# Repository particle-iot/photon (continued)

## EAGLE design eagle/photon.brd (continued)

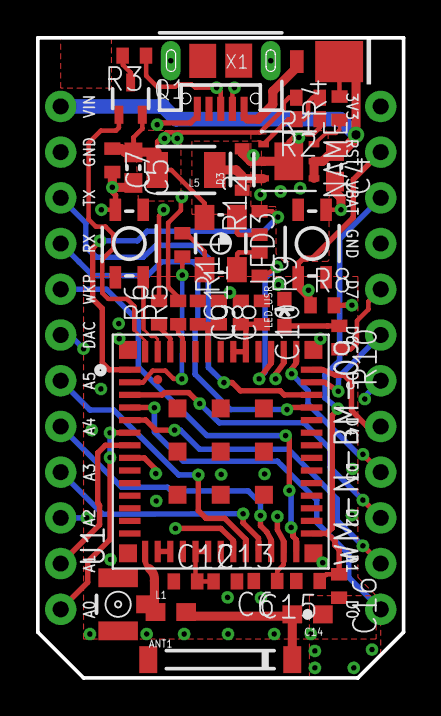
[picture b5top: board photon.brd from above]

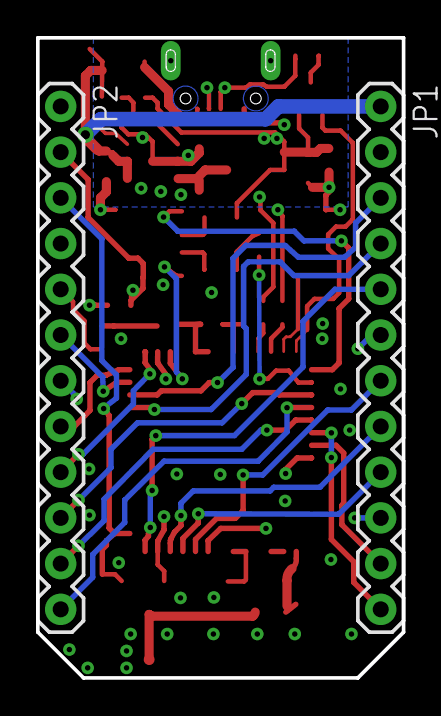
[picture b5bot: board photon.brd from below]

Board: 4 copper layers, 20.3 x 35.6 mm, 41 parts (2 on the bottom side), 46 nets.

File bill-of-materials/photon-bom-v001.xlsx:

| SPARK SKU |  | Spark Photon
 | BOM VERSION |  | v0.0.1
 | Qty | Device | Minimum Specification | Package/Case | Part Designator | MFG. | MFG. PN
 | 1 | ANTENNA | 2.4GHz, Ceramic | 8mm x 1mm | ANT1 | ACX | US PN = 2500AT44M0400E Asia PN = AT8010-E2R9HAA
 | 2 | CERAMIC CAPACITOR | 22uF, Ceramic, 10V, 10%, X5R | 0603 | C4, C5
 | 6 | CERAMIC CAPACITOR | 0.1uF, Ceramic, 10V, 10%, X5R | 0402 | C6, C7, C8, C10, C12, C16
 | 4 | CERAMIC CAPACITOR | 10uF, Ceramic, 10V, 10%, X5R | 0402 | C9, C11, C13, C15
 | 1 | CERAMIC CAPACITOR (RF) | 0.8pF, Ceramic, 25V, ±0.25pF | 0603 | C14 | Johanson Technology Inc. | 251R14S0R8BV4T
 | 1 | CONNECTOR | USB Micro-B with tabs and slots | USB-MICROB | X1 | Kaweei | CMCUSB-5BFM2G-01-D
 | 1 | CONNECTOR | uFL Connector | SMD | X2 | Kaweei | P1163-0140R
 | 1 | DIODE | Diode, Schottky, 30V, 3A | DO-220AA | D1 | Vishay | SS3P3-M3/84A
 | 1 | DIODE | Diode, Schottky, 23V, 1A | SOD323 | D3 | STMicroelectronics | BAT20JFILM
 | 1 | DIODE (LED) | Blue, SMD | 0603 | LED_USR | Everlight | 19-217/BHC-ZL1M2RY/3T
 | 1 | DIODE (LED) | LED RGB, SMD | 4-PLCC (3.2 mm x 2.8mm) | LED3 | Cree | CLVBA-FKA-CAEDH8BBB7A363
 | 2 | HEADER | Single String, 1.2" Mating Length | 0.1" 12-pin | JP1, JP2 | Kaweei | CP25411-12G-S116-A
 | 1 | INDUCTOR | 1.0uH, 2050mA | 1210 | L5 | Murata | LQH32PN1R0NN0L
 | 1 | INDUCTOR (RF) | 3.3nH, RF inductor | 0603 | L1 | Johanson Technology Inc. | L-14C3N3SV4T
 | 1 | POWER REGULATOR | IC Buck Regulator, 1A | WSON-6-PAD (3x3) | U2 | Texas Instruments | LMR10510YSDE/NOPB
 | 1 | RESISTOR | 45.2K, 1% | 0402 | R1
 | 2 | RESISTOR | 100K, 1% | 0402 | R2, R4
 | 1 | RESISTOR | 1K5, 5% | 0402 | R3
 | 2 | RESISTOR | 22R, 5% | 0402 | R5, R6
 | 1 | RESISTOR | 10K, 5% | 0402 | R8
 | 4 | RESISTOR | 1K, 5% | 0402 | R9, R10, R11, R12
 | 2 | SWITCH | Button, 160gf | 3.6mm x 3.1mm | MODE, RESET | Haoyu | TS-1185A-C
 | 1 | TRANSISTOR (PNP) | DDTA113ZUA | SOT-323 | Q1 | Diodes, Inc. | 2DB1689-7
 | 1 | WI-FI + MCU | Broadcom Wi-FI + STM32 MCU | Custom USI SMD | U1 | USI | WM-N-BM-09

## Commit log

2014-11-12 Updated License
2014-12-04 updated smd footprint library for the photon
2014-12-04 removed artifacts from the foot lib
2014-12-26 updated pinmap and added extra documentation for P0 module
2015-01-01 D0 - D7 instead of D0 - D1
    I guess, this was a typo and should be D0 - D7
2015-01-02 updated Spark EAGLE library
2015-01-02 added cam and drc files
2015-01-02 new directory structure
2015-01-02 added two new photon designs with rf test boards
2015-01-02 file cleanup
2015-01-02 updated README.md with v010 info
2015-01-02 versioning bom v001
2015-01-02 versioning pinmap v010
2015-01-16 updated RGB LED datasheet to 2mm version
2015-01-24 added photon-bom-v010.xlsx
2015-01-24 added pdfs of v010 schematics
2015-01-28 updated L5 desc and size and C4, C5 package size
2015-02-20 Updated 2mm RGB LED and castellated header soldermask
2015-03-02 added P1 / WM-N-BM-14 pinmap and EAGLE library files
2015-03-13 Added in photon SMD footprint
    Some things to be finalised before i introduce more variant:
    1.) Pads numbering. No. 1 starts with VIN and 24 will be 3V3. Yes/no?
    2.) The pads are slightly extended to facilitate hand soldering.
    Larger/smaller?
    3.) 2 variants i have in mind: Through-hole and SMD + through-hole
    4.) Are the naming for the symbol ok?
2015-03-23 updated photon pinmap
2015-03-27 Photon v019 design files added
2015-03-27 Spark library updated, PHOTON-TOP-SS-2 and TP60_BOT added
2015-03-27 added v019 bom
2015-03-27 updated datasheets
2015-03-31 corrected bom qty for 10pF caps (3x)
2015-04-09 updated P1 pinmap
2015-05-01 Spark library updated
    Added Photon footprint - single and stackable.
2015-05-08 Added PHOTON and PHOTON_SMD devices to Spark.lbr
2015-06-07 Photon P1 Device Added
2015-06-07 Updated WM-N-BM-14 device (P1 Module)
2015-06-07 Photon v1.0.0 design files
2015-06-18 updated pinmap
2016-01-28 Designed by Particle.
2017-01-11 Replaced type number of RGB led with the correct one
2018-01-26 STM datasheet update
2018-02-06 Add a space in `# License` so the Markdown is proper
